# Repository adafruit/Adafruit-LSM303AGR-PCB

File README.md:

## Adafruit LSM303AGR Triple-axis Accelerometer+Magnetometer PCB

<a href="http://www.adafruit.com/products/4413"><br/>
Click here to purchase one from the Adafruit shop</a>

PCB files for the Adafruit LSM303AGR Triple-axis Accelerometer+Magnetometer. 

Format is EagleCAD schematic and board layout
* https://www.adafruit.com/product/4413

### Description

The LSM303 breakout board combines a magnetometer/compass module with a triple-axis accelerometer to make a compact navigation subsystem. The I2C interface is compatible with both 3.3v and 5v processors and the two pins can be shared by other I2C devices. Combined with a 3-axis gyro such as the L3GD20, you have all the sensors you need for a complete IMU (Inertial Measurement Unit) for use in aerial, terrestrial or marine navigation.

### License

Adafruit invests time and resources providing this open source design, please support Adafruit and open-source hardware by purchasing products from [Adafruit](https://www.adafruit.com)!

Designed by Bryan Siepert for Adafruit Industries.

Creative Commons Attribution/Share-Alike, all text above must be included in any redistribution. 
See license.txt for additional details.

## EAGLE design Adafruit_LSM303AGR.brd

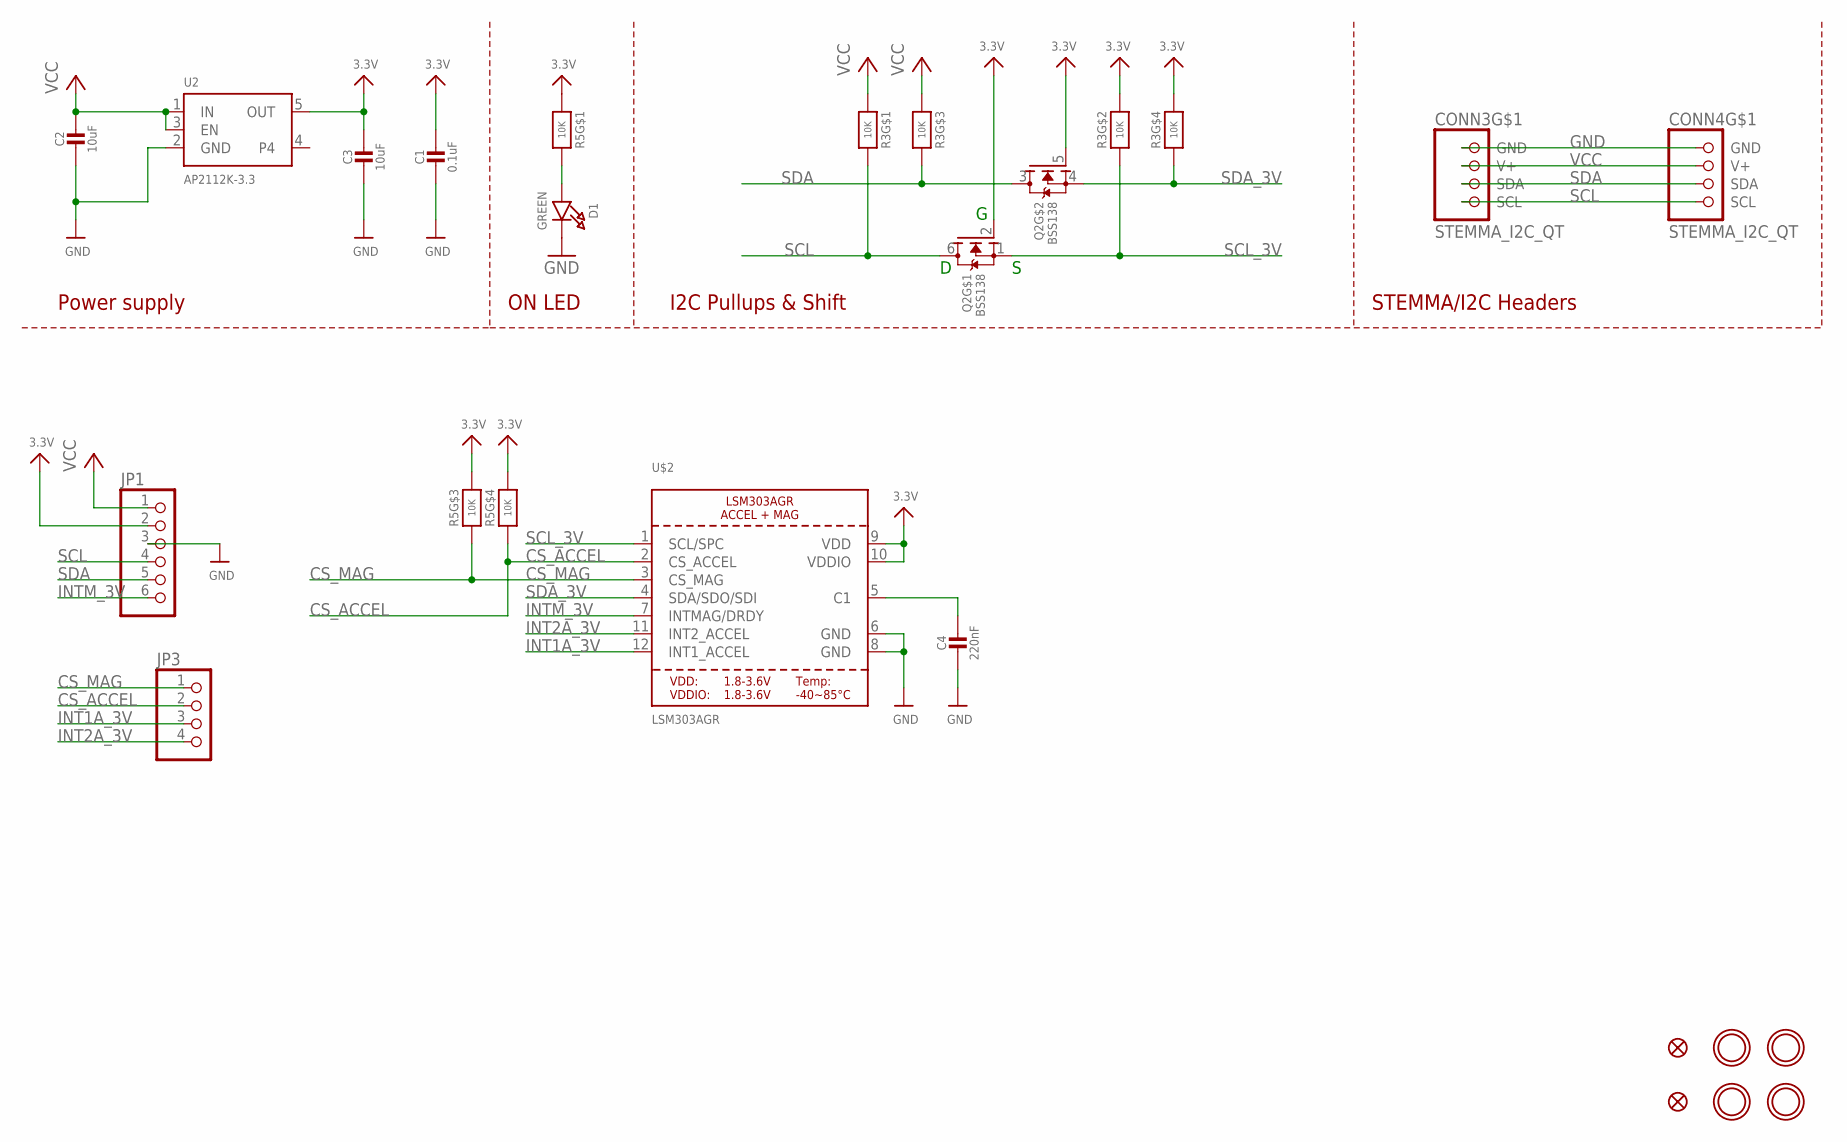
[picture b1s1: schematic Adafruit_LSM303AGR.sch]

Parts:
C1: 0.1uF; 0603-NO@1
C2: 10uF; 0805-NO
C3: 10uF; 0805_10MGAP
C4: 220nF; 0603-NO@1
CONN3, CONN4: STEMMA_I2C_QT; JST_SH4
D1: GREEN; CHIPLED_0603_NOOUTLINE
FID3, FID4: FIDUCIAL_1MM
JP1: HEADER-1X670MIL; 1X06_ROUND_70
JP3: HEADER-1X4ROUND; 1X04_ROUND
Q2: BSS138; SOT363
R3, R5: 10K; RESPACK_4X0603
U2: AP2112K-3.3; SOT23-5
U$1, U$17, U$19, U$21: MOUNTINGHOLE2.5; MOUNTINGHOLE_2.5_PLATED
U$2: LSM303AGR; LGA12_2X2MM

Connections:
3.3V: C1.1, C3.1, JP1.2, Q2.2 (G), Q2.5 (G), R3.2 (1), R3.4 (1), R5.1, R5.5 (2), R5.6 (2), U2.5 (OUT), U$2.9 (VDD), U$2.10 (VDDIO)
CS_ACCEL: JP3.2, R5.4 (1), U$2.2 (CS_ACCEL)
CS_MAG: JP3.1, R5.3 (1), U$2.3 (CS_MAG)
GND: C1.2, C2.2, C3.2, C4.2, CONN3.1 (GND), CONN4.1 (GND), D1.C, JP1.3, U2.2 (GND), U$2.6 (GND), U$2.8 (GND)
INT1A_3V: JP3.3, U$2.12 (INT1_ACCEL)
INT2A_3V: JP3.4, U$2.11 (INT2_ACCEL)
INTM_3V: JP1.6, U$2.7 (INTMAG/DRDY)
unnamed: D1.A, R5.8 (2)
unnamed: C4.1, U$2.5 (C1)
SCL: CONN3.4 (SCL), CONN4.4 (SCL), JP1.4, Q2.6 (D), R3.8 (2)
SCL_3V: Q2.1 (S), R3.7 (2), U$2.1 (SCL/SPC)
SDA: CONN3.3 (SDA), CONN4.3 (SDA), JP1.5, Q2.3 (D), R3.6 (2)
SDA_3V: Q2.4 (S), R3.5 (2), U$2.4 (SDA/SDO/SDI)
VCC: C2.1, CONN3.2 (V+), CONN4.2 (V+), JP1.1, R3.1, R3.3 (1), U2.1 (IN), U2.3 (EN)

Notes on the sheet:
I2C Pullups & Shift
STEMMA/I2C Headers
ON LED
Power supply

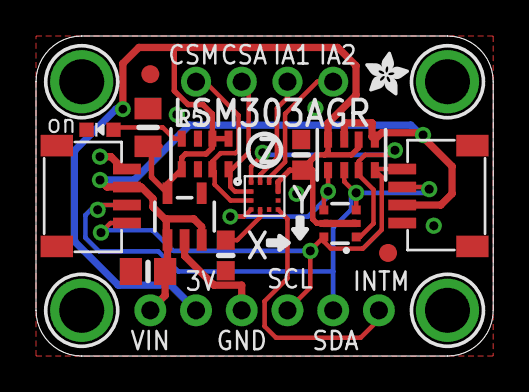
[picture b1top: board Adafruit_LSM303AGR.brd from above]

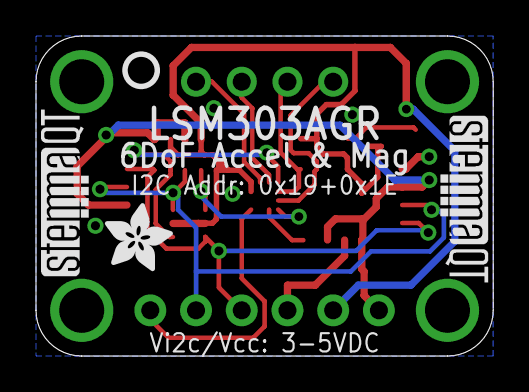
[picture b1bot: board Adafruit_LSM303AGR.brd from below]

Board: 2 copper layers, 25.4 x 17.8 mm, 25 parts (4 on the bottom side), 14 nets.

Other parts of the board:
U$20: ADAFRUIT_3.5MM
U$25: PCBFEAT-REV-040
U$30, U$31: STEMMAQT
U$40: ADAFRUIT_2.5MM

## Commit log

2019-11-06 updating product pic

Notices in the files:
parts and their libraries:
microbuilder: This work is placed in the public domain, and may be freely used for commercial and non-commercial work with the following conditions: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
